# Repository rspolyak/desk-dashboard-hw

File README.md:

# desk-dashboard-hw

A small ESP32-S3 board that plugs onto the 14-pin header of an **MSP3526** 3.5" IPS
capacitive touchscreen (ST7796 + FT6336U) and turns it into a desk dashboard.
Powered over USB-C (5 V). KiCad 10 project.

Corresponding firmware repository: [desk-dashboard-fw](https://github.com/rspolyak/desk-dashboard-fw)

**Status:** schematic and PCB finished (ERC 0 errors, DRC 0 errors, fully routed).
Board tested. No hardware issues found

## Features
- ESP32-S3-WROOM-1-N16R8 (16 MB flash, 8 MB octal PSRAM), native USB on the USB-C connector
- Plugs straight into the display's 14-pin 2.54 mm header, no cables; two optional M3 standoffs
- Ambient light sensor (ALS-PT19) for automatic backlight control
- SHT40 temperature / humidity sensor on its own I²C bus
- BOOT and RESET buttons
- 5 V to 3.3 V buck (TLV62569), USB ESD protection (USBLC6-2SC6), 1.1 A PTC and TVS on VBUS

## Board
- 41.5 x 35 mm, 2 layers, 1.6 mm, black solder mask, white silkscreen
- The ESP32 antenna overhangs the right board edge by 6 mm (Espressif's preferred placement)
- J2 (display socket) is on the display-facing side; all other parts face outward

## Design notes
- The display is powered from **5 V**: its LDO also feeds the backlight, which would be dim at 3.3 V.
- The display's touch I²C has 10 k pull-ups to 5 V, so two BSS138 level shifters (Q1 SCL, Q2 SDA)
  keep 5 V away from the ESP32-S3.
- The SHT40 is on a separate I²C controller from the touch panel.
- The light sensor is on ADC1 (ADC2 conflicts with Wi-Fi).

## Parts
All parts were in stock at JLCPCB when the design was finished. Each schematic symbol carries an
`LCSC` field with its part number.

| Ref | Part | LCSC |
|---|---|---|
| U1 | ESP32-S3-WROOM-1-N16R8 | C2913202 |
| U2 | TLV62569DBVR | C141836 |
| U3 | USBLC6-2SC6 | C2687116 |
| U4 | SHT40-AD1B-R2 | C2909890 |
| J1 | USB-C HRO TYPE-C-31-M-12 | C165948 |
| J2 | 1x14 female header, 2.54 mm, 8.5 mm | C2897377 |
| Q1, Q2 | BSS138 | C78284 |
| Q3 | ALS-PT19-315C | C146233 |

Passives, buttons, PTC, TVS and the inductor are listed in the schematic.

## Display
LCDwiki MSP3526 (3.5" IPS, 320x480, ST7796 + FT6336U), sold by several resellers

## License
MIT, see LICENSE

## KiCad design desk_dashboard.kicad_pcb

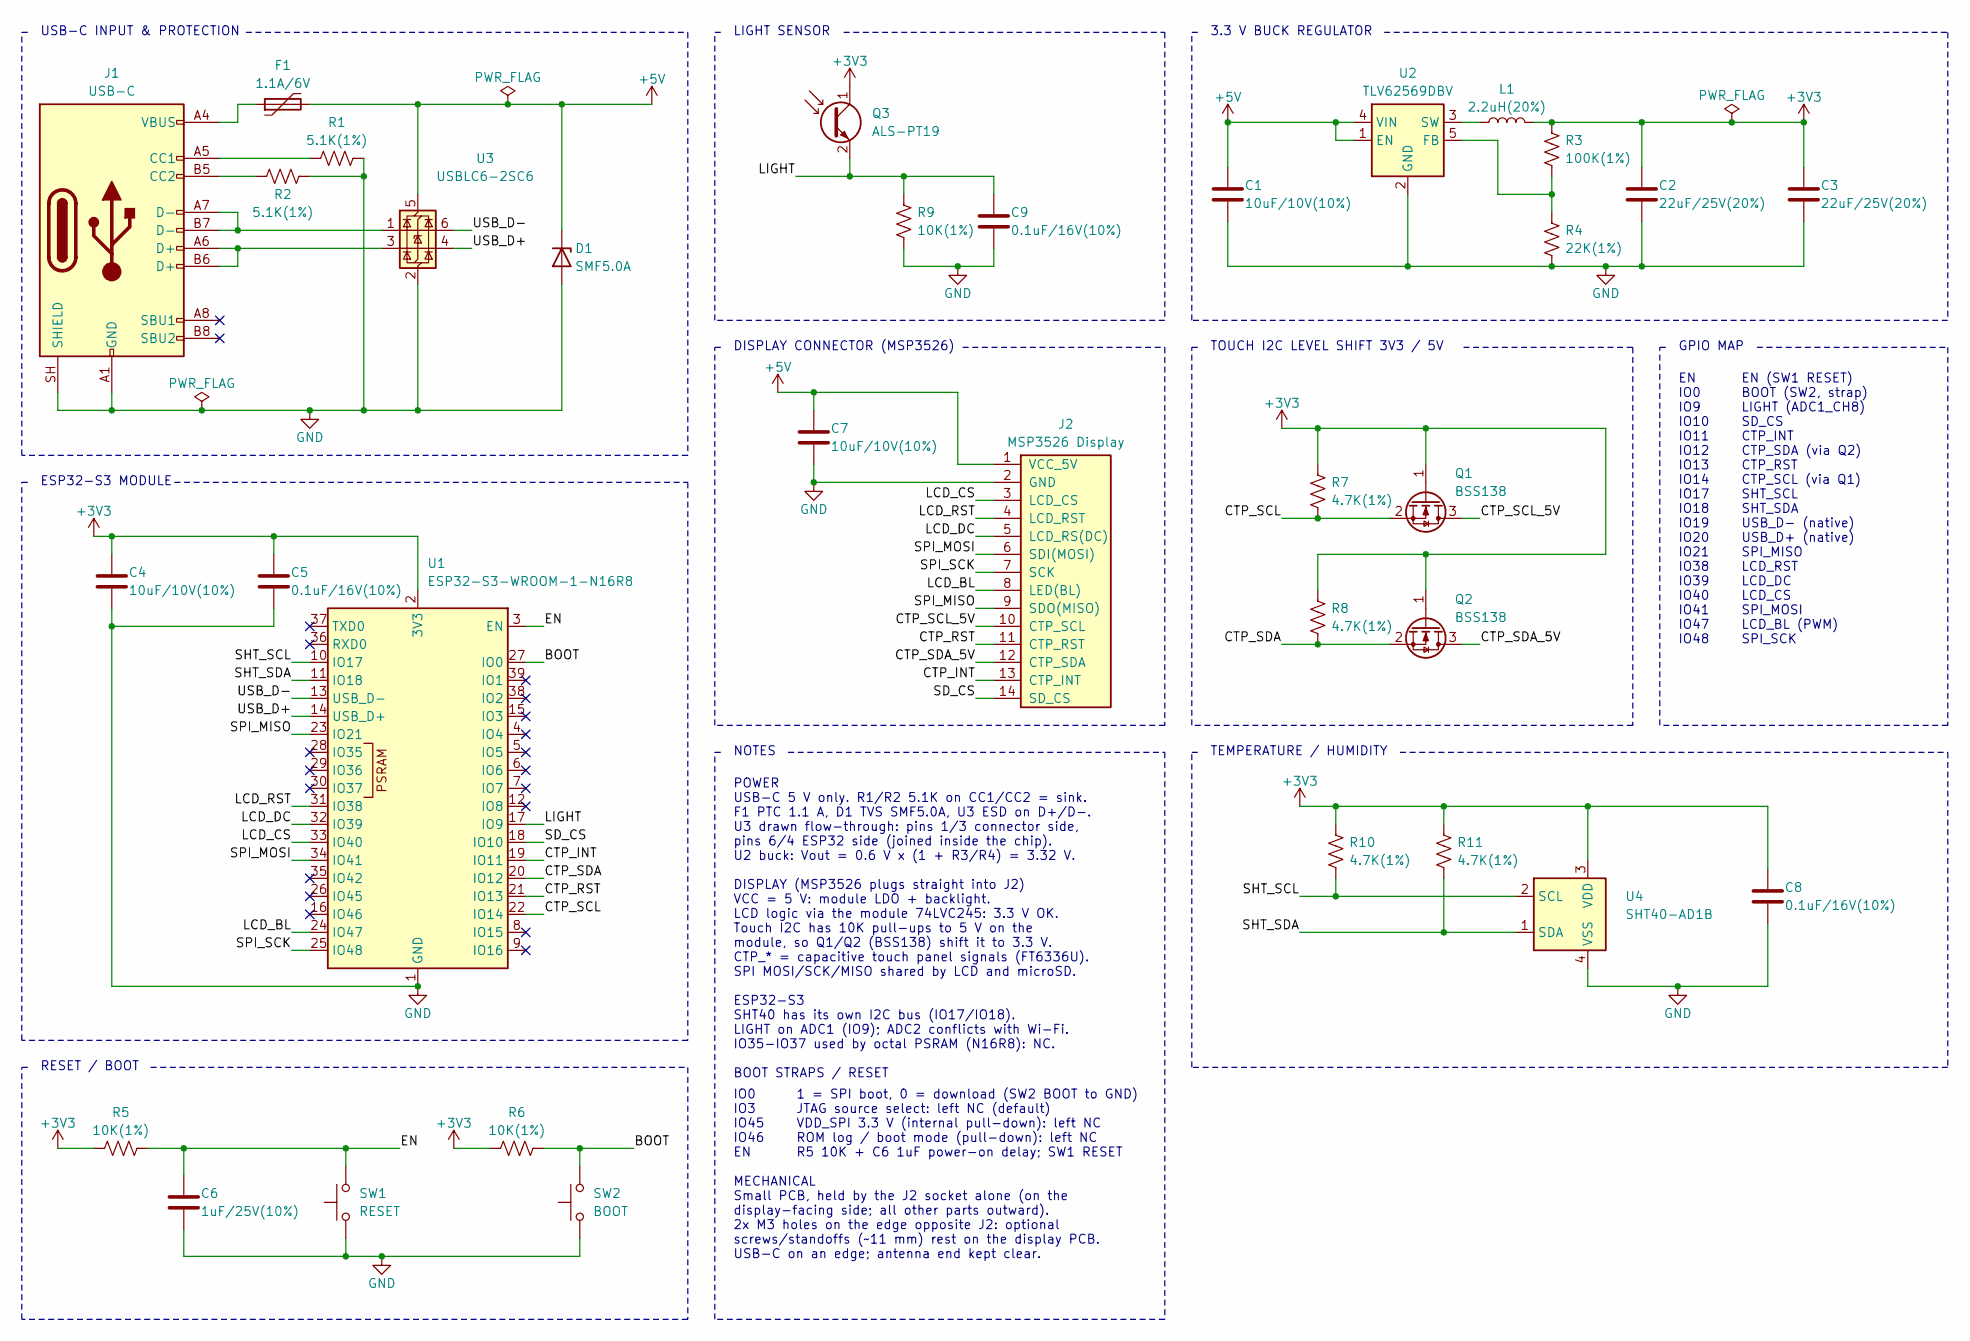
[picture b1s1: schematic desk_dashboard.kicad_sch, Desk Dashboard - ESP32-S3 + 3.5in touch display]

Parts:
C1, C4, C7: 10uF/10V(10%); C_0603_1608Metric; LCSC C19702
C2, C3: 22uF/25V(20%); C_0805_2012Metric; LCSC C45783
C5, C8, C9: 0.1uF/16V(10%); C_0402_1005Metric; LCSC C1525
C6: 1uF/25V(10%); C_0402_1005Metric; LCSC C52923
D1: SMF5.0A; D_SOD-123F; LCSC C193402
F1: 1.1A/6V; Fuse_1206_3216Metric; LCSC C20801
J1: USB-C; USB_C_Receptacle_HRO_TYPE-C-31-M-12; LCSC C165948
J2: MSP3526 Display; PinSocket_1x14_P2.54mm_Vertical; LCSC C2897377
L1: 2.2uH(20%); L_Sunlord_SWPA4030S; LCSC C36409
Q1, Q2: BSS138; SOT-23; LCSC C78284
Q3: ALS-PT19; Everlight_ALS-PT19; LCSC C146233
R1, R2: 5.1K(1%); R_0402_1005Metric; LCSC C25905
R3: 100K(1%); R_0402_1005Metric; LCSC C25741
R4: 22K(1%); R_0402_1005Metric; LCSC C25768
R5, R6, R9: 10K(1%); R_0402_1005Metric; LCSC C25744
R7, R8, R10, R11: 4.7K(1%); R_0402_1005Metric; LCSC C25900
SW1: RESET; SW_Push_1P1T_XKB_TS-1187A; LCSC C318884
SW2: BOOT; SW_Push_1P1T_XKB_TS-1187A; LCSC C318884
U1: ESP32-S3-WROOM-1-N16R8; ESP32-S3-WROOM-1; LCSC C2913202
U2: TLV62569DBV; SOT-23-5; LCSC C141836
U3: USBLC6-2SC6; SOT-23-6; LCSC C2687116
U4: SHT40-AD1B; Sensirion_DFN-4_1.5x1.5mm_P0.8mm_SHT4x_NoCentralPad; LCSC C2909890

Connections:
+3V3: C2.1, C3.1, C4.1, C5.1, C8.1, L1.2, Q1.1 (G), Q2.1 (G), Q3.1 (C), R3.1, R5.1, R6.1, R7.1, R8.1, R10.1, R11.2, U1.2 (3V3), U4.3 (VDD)
+5V: C1.1, C7.1, D1.1 (K), F1.2, J2.1 (VCC_5V), U2.1 (EN), U2.4 (VIN), U3.5 (VBUS)
/BOOT: R6.2, SW2.2, U1.27 (IO0)
/CTP_INT: J2.13 (CTP_INT), U1.19 (IO11)
/CTP_RST: J2.11 (CTP_RST), U1.21 (IO13)
/CTP_SCL: Q1.2 (S), R7.2, U1.22 (IO14)
/CTP_SCL_5V: J2.10 (CTP_SCL), Q1.3 (D)
/CTP_SDA: Q2.2 (S), R8.2, U1.20 (IO12)
/CTP_SDA_5V: J2.12 (CTP_SDA), Q2.3 (D)
/EN: C6.1, R5.2, SW1.2, U1.3 (EN)
/LCD_BL: J2.8 (LED(BL)), U1.24 (IO47)
/LCD_CS: J2.3 (LCD_CS), U1.33 (IO40)
/LCD_DC: J2.5 (LCD_RS(DC)), U1.32 (IO39)
/LCD_RST: J2.4 (LCD_RST), U1.31 (IO38)
/LIGHT: C9.1, Q3.2 (E), R9.1, U1.17 (IO9)
/SD_CS: J2.14 (SD_CS), U1.18 (IO10)
/SHT_SCL: R10.2, U1.10 (IO17), U4.2 (SCL)
/SHT_SDA: R11.1, U1.11 (IO18), U4.1 (SDA)
/SPI_MISO: J2.9 (SDO(MISO)), U1.23 (IO21)
/SPI_MOSI: J2.6 (SDI(MOSI)), U1.34 (IO41)
/SPI_SCK: J2.7 (SCK), U1.25 (IO48)
/USB_D+: U1.14 (USB_D+), U3.4 (I/O2)
/USB_D-: U1.13 (USB_D-), U3.6 (I/O1)
GND: C1.2, C2.2, C3.2, C4.2, C5.2, C6.2, C7.2, C8.2, C9.2, D1.2 (A), J1.A1 (GND), J1.A12 (GND), J1.B1 (GND), J1.B12 (GND), J1.SH (SHIELD), J2.2 (GND), R1.2, R2.2, R4.2, R9.2, SW1.1, SW2.1, U1.1 (GND), U1.40 (GND), U1.41 (GND), U2.2 (GND), U3.2 (GND), U4.4 (VSS)
unnamed: F1.1, J1.A4 (VBUS), J1.A9 (VBUS), J1.B4 (VBUS), J1.B9 (VBUS)
unnamed: J1.A5 (CC1), R1.1
unnamed: J1.B5 (CC2), R2.1
unnamed: J1.A6 (D+), J1.B6 (D+), U3.3 (I/O2)
unnamed: J1.A7 (D-), J1.B7 (D-), U3.1 (I/O1)
unnamed: R3.2, R4.1, U2.5 (FB)
unnamed: L1.1, U2.3 (SW)

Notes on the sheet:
EN IO0 IO9 IO10 IO11 IO12 IO13 IO14 IO17 IO18 IO19 IO20 IO21 IO38 IO39 IO40 IO41 IO47 IO48
GPIO MAP
ESP32-S3 MODULE
IO0 IO3 IO45 IO46 EN
TOUCH I2C LEVEL SHIFT 3V3 / 5V
3.3 V BUCK REGULATOR
LIGHT SENSOR
TEMPERATURE / HUMIDITY
USB-C INPUT & PROTECTION
1 = SPI boot, 0 = download (SW2 BOOT to GND) JTAG source select: left NC (default) VDD_SPI 3.3 V (internal pull-down): left NC ROM log / boot mode (pull-down): left NC R5 10K + C6 1uF power-on delay; SW1 RESET
NOTES
MECHANICAL Small PCB, held by the J2 socket alone (on the display-facing side; all other parts outward). 2x M3 holes on the edge opposite J2: optional screws/standoffs (~11 mm) rest on the display PCB. USB-C on an edge; antenna end kept clear.
POWER USB-C 5 V only. R1/R2 5.1K on CC1/CC2 = sink. F1 PTC 1.1 A, D1 TVS SMF5.0A, U3 ESD on D+/D-. U3 drawn flow-through: pins 1/3 connector side, pins 6/4 ESP32 side (joined inside the chip). U2 buck: Vout = 0.6 V x (1 + R3/R4) = 3.32 V. DISPLAY (MSP3526 plugs straight into J2) VCC = 5 V: module L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
EN (SW1 RESET) BOOT (SW2, strap) LIGHT (ADC1_CH8) SD_CS CTP_INT CTP_SDA (via Q2) CTP_RST CTP_SCL (via Q1) SHT_SCL SHT_SDA USB_D- (native) USB_D+ (native) SPI_MISO LCD_RST LCD_DC LCD_CS SPI_MOSI LCD_BL (PWM) SPI_SCK
RESET / BOOT
DISPLAY CONNECTOR (MSP3526)

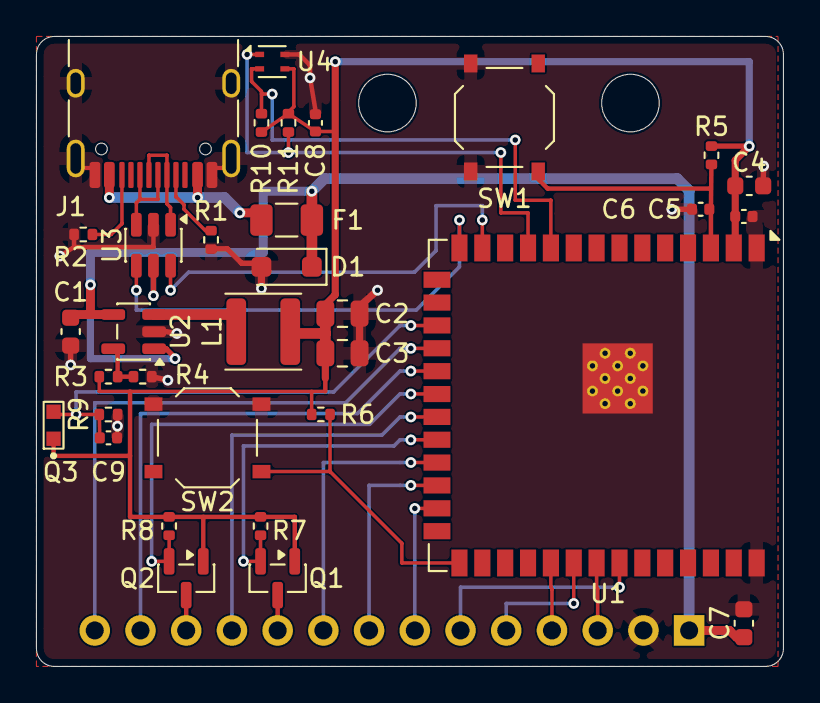
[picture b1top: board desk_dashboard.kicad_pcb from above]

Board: 2 copper layers, 41.5 x 35.0 mm, 36 parts (1 on the bottom side), 31 nets.

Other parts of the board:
H1, H2: MountingHole_3.2mm_M3
